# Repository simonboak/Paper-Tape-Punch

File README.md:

# Paper Tape Punch
My DIY paper tape punch project, this repo contains the Arduino source code and PDF schematics

[Full writeup on my blog](https://unimplementedtrap.com/paper-tape-punch)

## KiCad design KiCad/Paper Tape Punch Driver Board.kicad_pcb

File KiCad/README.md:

# Paper Tape Punch - KiCad Files
For full authenticity you'll want the [Bedstead font](https://bjh21.me.uk/bedstead/).

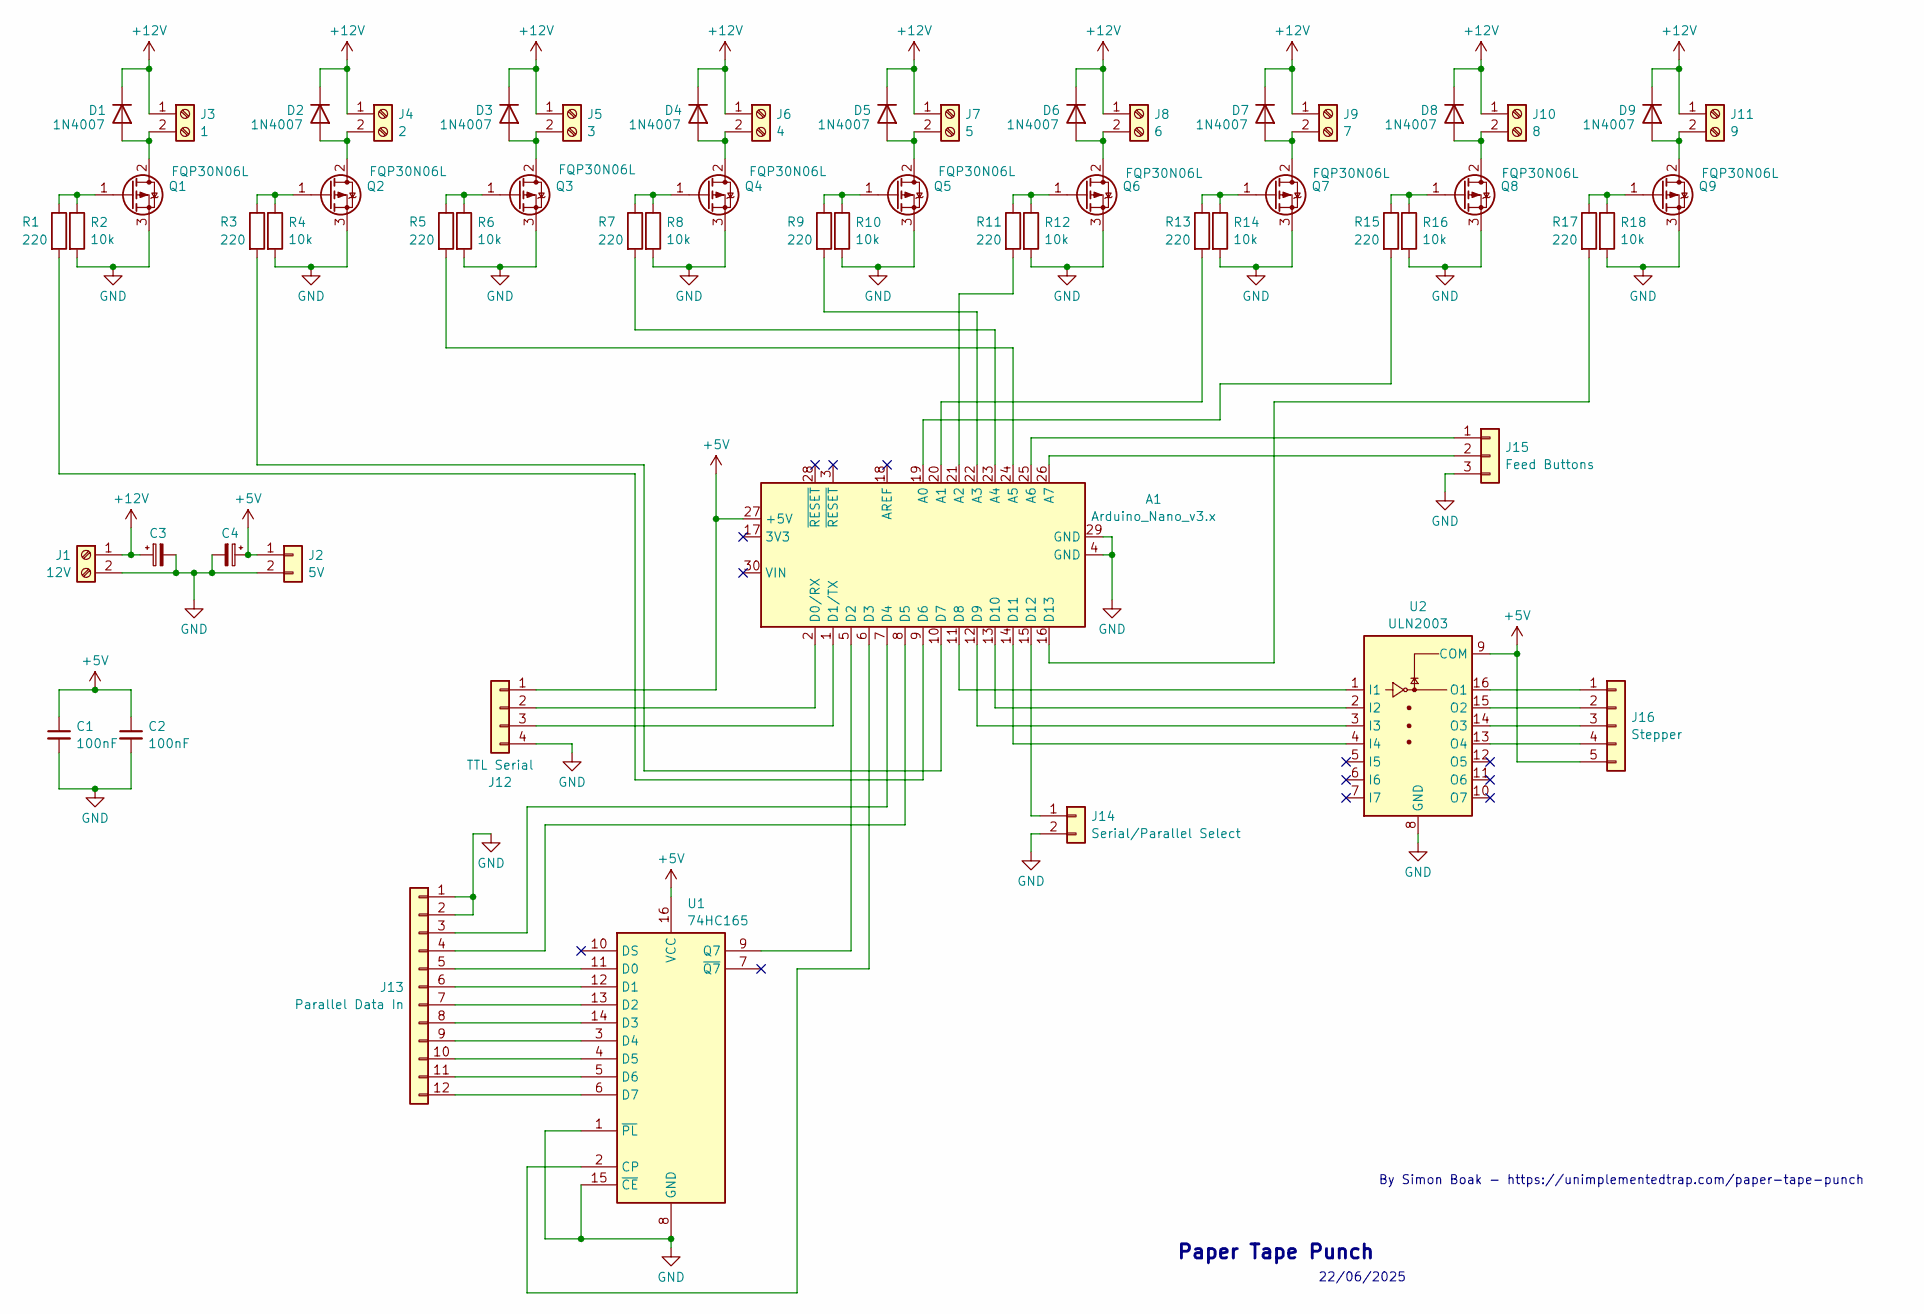
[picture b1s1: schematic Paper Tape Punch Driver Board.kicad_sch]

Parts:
A1: Arduino_Nano_v3.x; Arduino_Nano
C1, C2: 100nF; C_Rect_L9.0mm_W2.5mm_P7.50mm_MKT
C3: C_Polarized_Small; CP_Radial_D10.0mm_P5.00mm
C4: C_Polarized_Small; CP_Radial_D8.0mm_P3.80mm
D1, D2, D3, D4, D5, D6, D7, D8, D9: 1N4007; D_DO-41_SOD81_P10.16mm_Horizontal
J1: 12V; TerminalBlock_RND_205-00012_1x02_P5.00mm_Horizontal
J2: 5V; Molex_KK-254_AE-6410-02A_1x02_P2.54mm_Vertical
J3: 1; TerminalBlock_RND_205-00012_1x02_P5.00mm_Horizontal
J4: 2; TerminalBlock_RND_205-00012_1x02_P5.00mm_Horizontal
J5: 3; TerminalBlock_RND_205-00012_1x02_P5.00mm_Horizontal
J6: 4; TerminalBlock_RND_205-00012_1x02_P5.00mm_Horizontal
J7: 5; TerminalBlock_RND_205-00012_1x02_P5.00mm_Horizontal
J8: 6; TerminalBlock_RND_205-00012_1x02_P5.00mm_Horizontal
J9: 7; TerminalBlock_RND_205-00012_1x02_P5.00mm_Horizontal
J10: 8; TerminalBlock_RND_205-00012_1x02_P5.00mm_Horizontal
J11: 9; TerminalBlock_RND_205-00012_1x02_P5.00mm_Horizontal
J12: TTL Serial; Molex_KK-254_AE-6410-04A_1x04_P2.54mm_Vertical
J13: Parallel Data In; IDC-Header_2x06_P2.54mm_Vertical
J14: Serial/Parallel Select; Molex_KK-254_AE-6410-02A_1x02_P2.54mm_Vertical
J15: Feed Buttons; Molex_KK-254_AE-6410-03A_1x03_P2.54mm_Vertical
J16: Stepper; JST_XH_B5B-XH-A_1x05_P2.50mm_Vertical
Q1, Q2, Q3, Q4, Q5, Q6, Q7, Q8, Q9: FQP30N06L; TO-220-3_Vertical
R1, R3, R5, R7, R9, R11, R13, R15, R17: 220; R_Axial_DIN0204_L3.6mm_D1.6mm_P7.62mm_Horizontal
R2, R4, R6, R8, R10, R12, R14, R16, R18: 10k; R_Axial_DIN0204_L3.6mm_D1.6mm_P7.62mm_Horizontal
U1: 74HC165; CERDIP-16_W7.62mm_SideBrazed_LongPads_Socket
U2: ULN2003; CERDIP-16_W7.62mm_SideBrazed_LongPads_Socket

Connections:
+5V: A1.27 (+5V), C1.1, C2.1, C4.1, J2.1, J12.1, J16.5, U1.16 (VCC), U2.9 (COM)
+12V: C3.1, D1.1 (K), D2.1 (K), D3.1 (K), D4.1 (K), D5.1 (K), D6.1 (K), D7.1 (K), D8.1 (K), D9.1 (K), J1.1, J3.1, J4.1, J5.1, J6.1, J7.1, J8.1, J9.1, J10.1, J11.1
GND: A1.4 (GND), A1.29 (GND), C1.2, C2.2, C3.2, C4.2, J1.2, J2.2, J12.4, J13.1, J13.2, J14.2, J15.3, Q1.3 (S), Q2.3 (S), Q3.3 (S), Q4.3 (S), Q5.3 (S), Q6.3 (S), Q7.3 (S), Q8.3 (S), Q9.3 (S), R2.2, R4.2, R6.2, R8.2, R10.2, R12.2, R14.2, R16.2, R18.2, U1.1 (~PL), U1.8 (GND), U1.15 (~CE), U2.8 (GND)
unnamed: A1.19 (A0), R15.2
unnamed: A1.20 (A1), R13.2
unnamed: A1.21 (A2), R11.2
unnamed: A1.22 (A3), R9.2
unnamed: A1.23 (A4), R7.2
unnamed: A1.24 (A5), R5.2
unnamed: A1.25 (A6), J15.1
unnamed: A1.26 (A7), J15.2
unnamed: A1.2 (D0/RX), J12.2
unnamed: A1.1 (D1/TX), J12.3
unnamed: A1.5 (D2), U1.9 (Q7)
unnamed: A1.6 (D3), U1.2 (CP)
unnamed: A1.7 (D4), J13.3
unnamed: A1.8 (D5), J13.4
unnamed: A1.9 (D6), R1.2
unnamed: A1.10 (D7), R3.2
unnamed: A1.11 (D8), U2.1 (I1)
unnamed: A1.12 (D9), U2.3 (I3)
unnamed: A1.13 (D10), U2.2 (I2)
unnamed: A1.14 (D11), U2.4 (I4)
unnamed: A1.15 (D12), J14.1
unnamed: A1.16 (D13), R17.2
unnamed: D1.2 (A), J3.2, Q1.2 (D)
unnamed: D2.2 (A), J4.2, Q2.2 (D)
unnamed: D3.2 (A), J5.2, Q3.2 (D)
unnamed: D4.2 (A), J6.2, Q4.2 (D)
unnamed: D5.2 (A), J7.2, Q5.2 (D)
unnamed: D6.2 (A), J8.2, Q6.2 (D)
unnamed: D7.2 (A), J9.2, Q7.2 (D)
unnamed: D8.2 (A), J10.2, Q8.2 (D)
unnamed: D9.2 (A), J11.2, Q9.2 (D)
unnamed: J13.5, U1.11 (D0)
unnamed: J13.6, U1.12 (D1)
unnamed: J13.7, U1.13 (D2)
unnamed: J13.8, U1.14 (D3)
unnamed: J13.9, U1.3 (D4)
unnamed: J13.10, U1.4 (D5)
unnamed: J13.11, U1.5 (D6)
unnamed: J13.12, U1.6 (D7)
unnamed: J16.1, U2.16 (O1)
unnamed: J16.2, U2.15 (O2)
unnamed: J16.3, U2.14 (O3)
unnamed: J16.4, U2.13 (O4)
unnamed: Q1.1 (G), R1.1, R2.1
unnamed: Q2.1 (G), R3.1, R4.1
unnamed: Q3.1 (G), R5.1, R6.1
unnamed: Q4.1 (G), R7.1, R8.1
unnamed: Q5.1 (G), R9.1, R10.1
unnamed: Q6.1 (G), R11.1, R12.1
unnamed: Q7.1 (G), R13.1, R14.1
unnamed: Q8.1 (G), R15.1, R16.1
unnamed: Q9.1 (G), R17.1, R18.1

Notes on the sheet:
Paper Tape Punch
22/06/2025
By Simon Boak - https://unimplementedtrap.com/paper-tape-punch

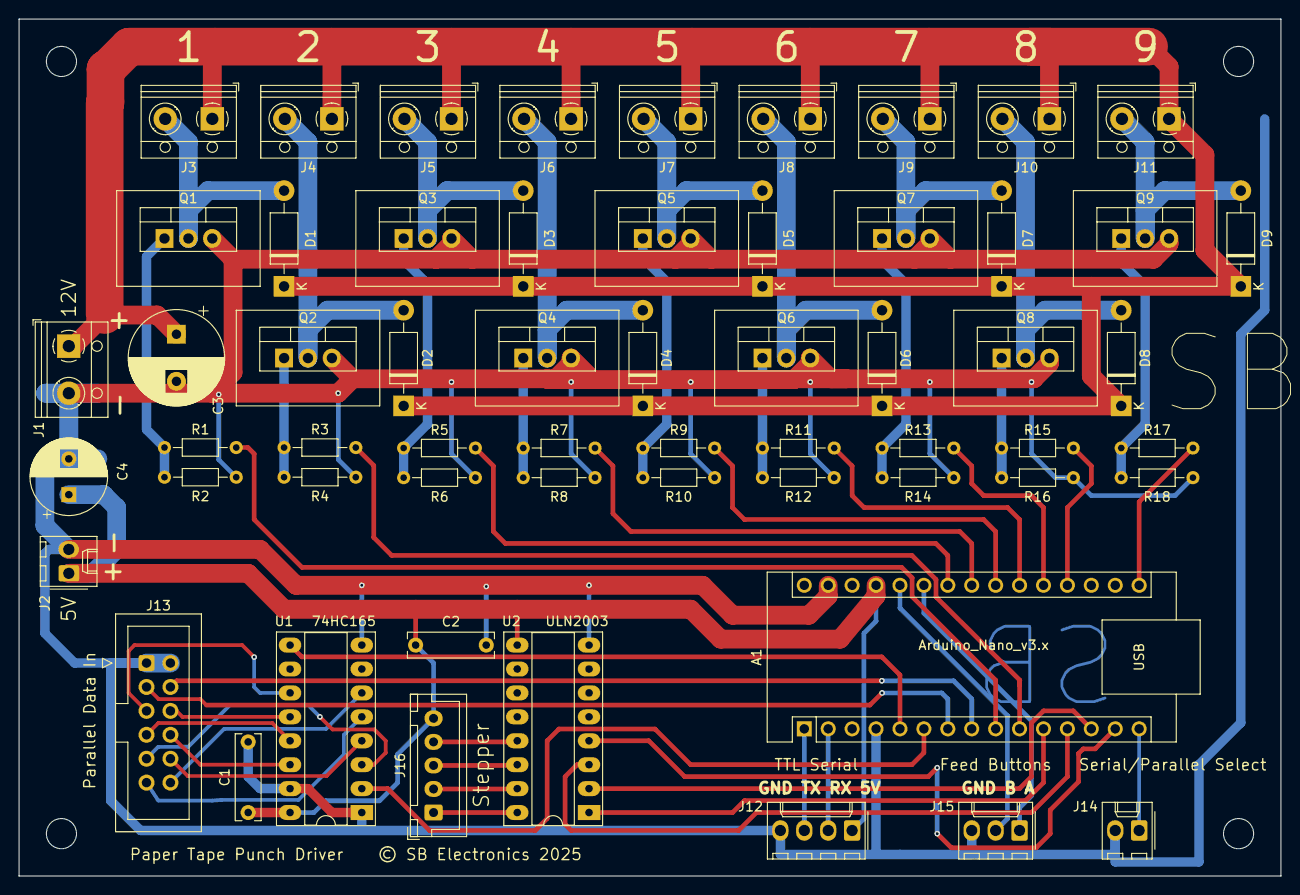
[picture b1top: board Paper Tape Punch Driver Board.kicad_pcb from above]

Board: 2 copper layers, 134.0 x 91.0 mm, 59 parts (0 on the bottom side), 55 nets.

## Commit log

2025-06-22 Adding project info
2025-06-23 Adding CAD files
2025-11-11 Adding KiCad project files

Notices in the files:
KiCad/Paper Tape Punch Driver Board.kicad_pcb:
Paper Tape Punch Driver © SB Electronics 2025
